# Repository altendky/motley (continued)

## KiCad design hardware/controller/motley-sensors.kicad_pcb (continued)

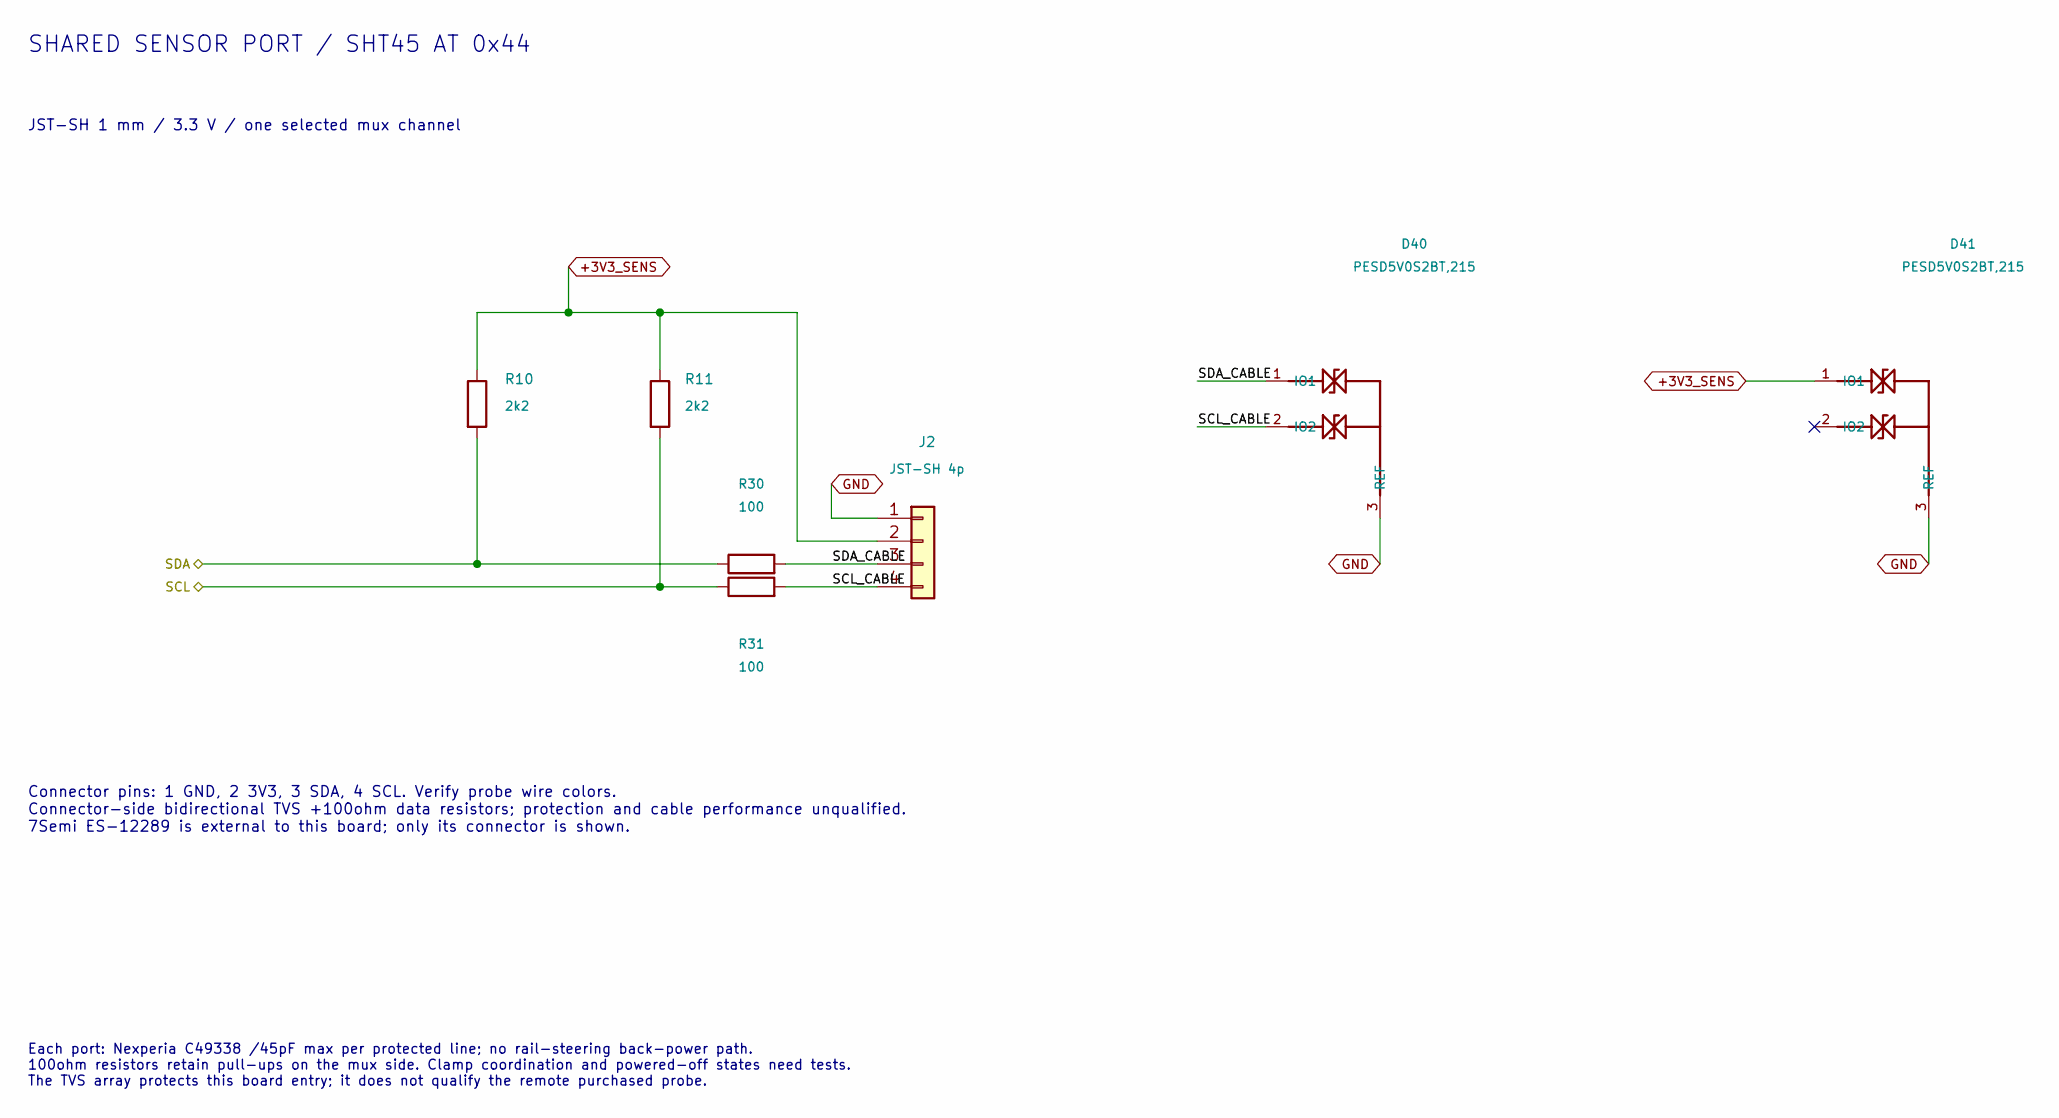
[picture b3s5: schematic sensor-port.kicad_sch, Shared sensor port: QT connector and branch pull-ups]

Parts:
D40, D41: PESD5V0S2BT,215; SOT-23
J2: JST-SH 4p; JST_SH_SM04B-SRSS-TB_1x04-1MP_P1.00mm_Horizontal
R10, R11: 2k2; R_0805_2012Metric
R30, R31: 100; R_0805_2012Metric

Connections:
+3V3_SENS: D41.1 (IO1), J2.2, R10.1, R11.1; also elsewhere on the board
/Sensor ports/Port 0/SCL_CABLE: D40.2 (IO2), J2.4, R31.2
/Sensor ports/Port 0/SDA_CABLE: D40.1 (IO1), J2.3, R30.2
GND: D40.3 (REF), D41.3 (REF), J2.1; also elsewhere on the board
SCL0: R11.2, R31.1; also elsewhere on the board
SDA0: R10.2, R30.1; also elsewhere on the board

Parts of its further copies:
D42, D43, D44, D45, D46, D47, D48, D49, D50, D51, D52, D53, D54, D55: PESD5V0S2BT,215; SOT-23
J3, J4, J5, J6, J7, J8, J9: JST-SH 4p; JST_SH_SM04B-SRSS-TB_1x04-1MP_P1.00mm_Horizontal
R12, R13, R14, R15, R16, R17, R18, R19, R20, R21, R22, R23, R24, R25: 2k2; R_0805_2012Metric
R32, R33, R34, R35, R36, R37, R38, R39, R40, R41, R42, R43, R44, R45: 100; R_0805_2012Metric

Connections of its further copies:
+3V3_SENS: D43.1 (IO1), D45.1 (IO1), D47.1 (IO1), D49.1 (IO1), D51.1 (IO1), D53.1 (IO1), D55.1 (IO1), J3.2, J4.2, J5.2, J6.2, J7.2, J8.2, J9.2, R12.1, R13.1, R14.1, R15.1, R16.1, R17.1, R18.1, R19.1, R20.1, R21.1, R22.1, R23.1, R24.1, R25.1; also elsewhere on the board
/Sensor ports/Port 1/SCL_CABLE: D42.2 (IO2), J3.4, R33.2
/Sensor ports/Port 1/SDA_CABLE: D42.1 (IO1), J3.3, R32.2
/Sensor ports/Port 2/SCL_CABLE: D44.2 (IO2), J4.4, R35.2
/Sensor ports/Port 2/SDA_CABLE: D44.1 (IO1), J4.3, R34.2
/Sensor ports/Port 3/SCL_CABLE: D46.2 (IO2), J5.4, R37.2
/Sensor ports/Port 3/SDA_CABLE: D46.1 (IO1), J5.3, R36.2
/Sensor ports/Port 4/SCL_CABLE: D48.2 (IO2), J6.4, R39.2
/Sensor ports/Port 4/SDA_CABLE: D48.1 (IO1), J6.3, R38.2
/Sensor ports/Port 5/SCL_CABLE: D50.2 (IO2), J7.4, R41.2
/Sensor ports/Port 5/SDA_CABLE: D50.1 (IO1), J7.3, R40.2
/Sensor ports/Port 6/SCL_CABLE: D52.2 (IO2), J8.4, R43.2
/Sensor ports/Port 6/SDA_CABLE: D52.1 (IO1), J8.3, R42.2
/Sensor ports/Port 7/SCL_CABLE: D54.2 (IO2), J9.4, R45.2
/Sensor ports/Port 7/SDA_CABLE: D54.1 (IO1), J9.3, R44.2
GND: D42.3 (REF), D43.3 (REF), D44.3 (REF), D45.3 (REF), D46.3 (REF), D47.3 (REF), D48.3 (REF), D49.3 (REF), D50.3 (REF), D51.3 (REF), D52.3 (REF), D53.3 (REF), D54.3 (REF), D55.3 (REF), J3.1, J4.1, J5.1, J6.1, J7.1, J8.1, J9.1; also elsewhere on the board
SCL1: R13.2, R33.1; also elsewhere on the board
SCL2: R15.2, R35.1; also elsewhere on the board
SCL3: R17.2, R37.1; also elsewhere on the board
SCL4: R19.2, R39.1; also elsewhere on the board
SCL5: R21.2, R41.1; also elsewhere on the board
SCL6: R23.2, R43.1; also elsewhere on the board
SCL7: R25.2, R45.1; also elsewhere on the board
SDA1: R12.2, R32.1; also elsewhere on the board
SDA2: R14.2, R34.1; also elsewhere on the board
SDA3: R16.2, R36.1; also elsewhere on the board
SDA4: R18.2, R38.1; also elsewhere on the board
SDA5: R20.2, R40.1; also elsewhere on the board
SDA6: R22.2, R42.1; also elsewhere on the board
SDA7: R24.2, R44.1; also elsewhere on the board

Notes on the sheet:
JST-SH 1 mm / 3.3 V / one selected mux channel
Connector pins: 1 GND, 2 3V3, 3 SDA, 4 SCL. Verify probe wire colors. Connector-side bidirectional TVS +100ohm data resistors; protection and cable performance unqualified. 7Semi ES-12289 is external to this board; only its connector is shown.
SHARED SENSOR PORT / SHT45 AT 0x44
Each port: Nexperia C49338 /45pF max per protected line; no rail-steering back-power path. 100ohm resistors retain pull-ups on the mux side. Clamp coordination and powered-off states need tests. The TVS array protects this board entry; it does not qualify the remote purchased probe.

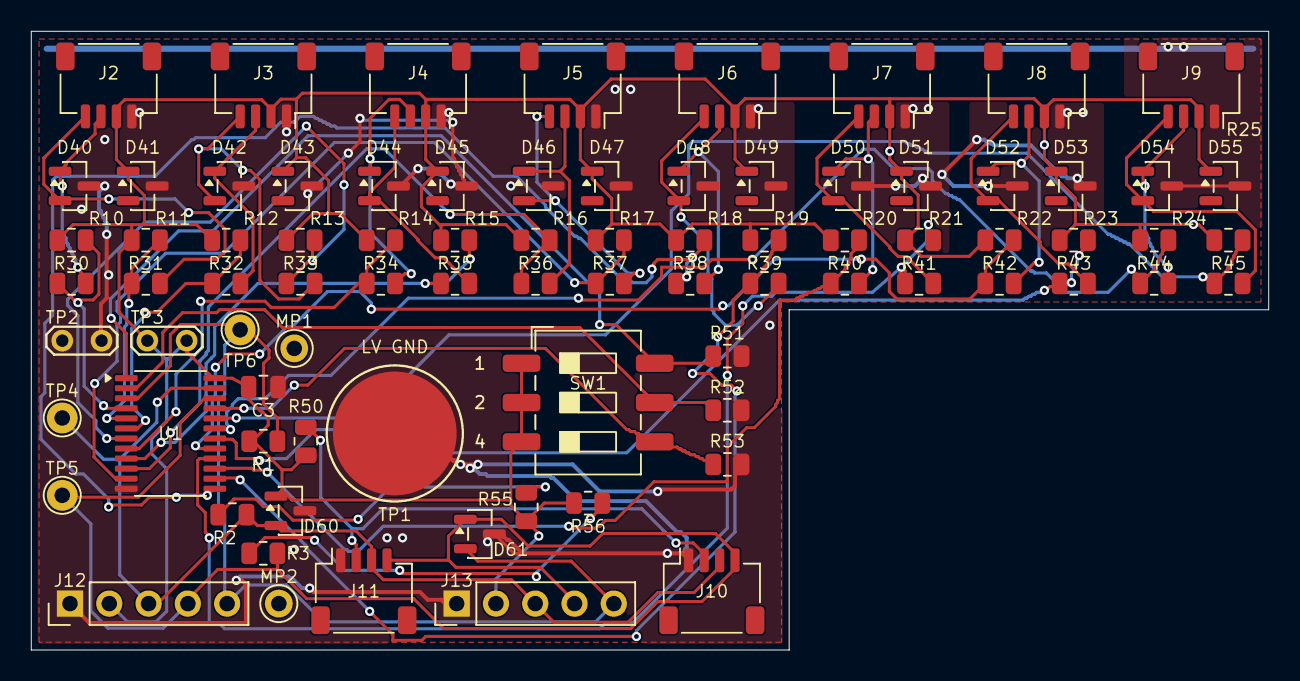
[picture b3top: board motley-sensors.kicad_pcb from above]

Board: 4 copper layers, 80.0 x 40.0 mm, 82 parts (0 on the bottom side), 43 nets.

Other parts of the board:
MP1, MP2: PROVISIONAL isolated plated mechanical pin; Mechanical_Pin_PTH_Study
